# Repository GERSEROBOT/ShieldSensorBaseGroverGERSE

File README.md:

# SensorBaseGroverGERSE

If it is necessary to download the MyKiCad repository, it is a library and contains components that this project can use
	- https://github.com/pedro-ibs/MyKiCad

-------------------------------------------------------------------------------------------------------------------------------

The sensors for this shield find if the SensorBaseGrover repository
	- 123

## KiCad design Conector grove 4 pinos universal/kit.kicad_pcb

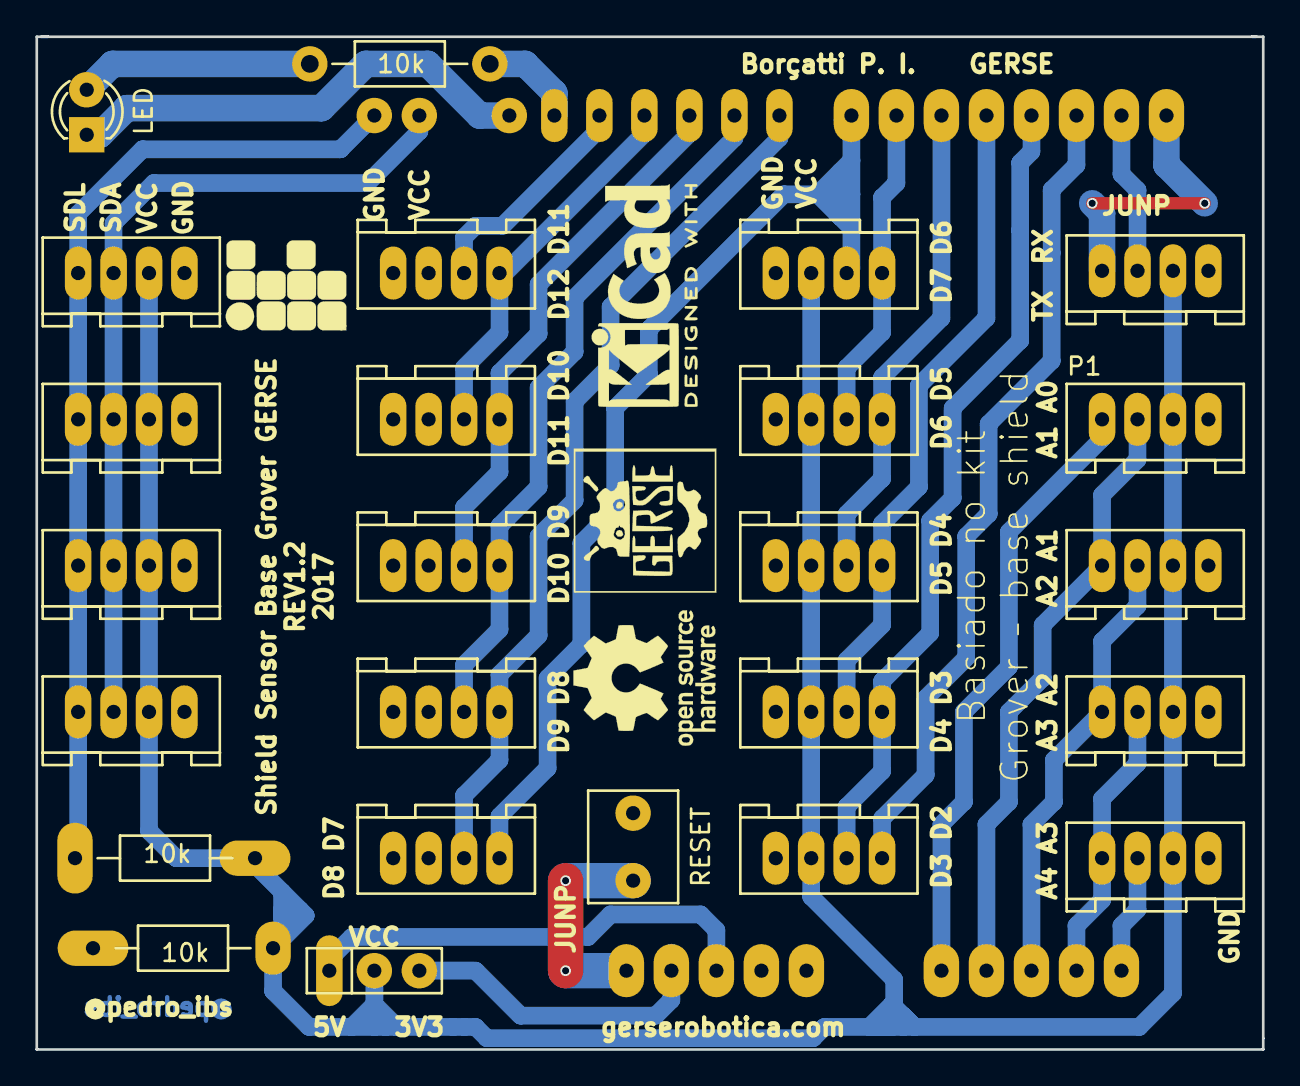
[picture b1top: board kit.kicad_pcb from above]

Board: 2 copper layers, 69.2 x 57.2 mm, 26 parts (0 on the bottom side), 26 nets.

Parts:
D1: LED; LED-3MM
IC1: ARDUINO_UNO
JP1: JUMP3; SW_Micro_SPST
P1: A0; Grove 4 pinos
P2: A1; Grove 4 pinos
P3: A2; Grove 4 pinos
P4: A3; Grove 4 pinos
P5: UART; Grove 4 pinos
P6: D2; Grove 4 pinos
P7: D3; Grove 4 pinos
P8: D4; Grove 4 pinos
P9: D5; Grove 4 pinos
P10: D6; Grove 4 pinos
P11: D7; Grove 4 pinos
P12: D8; Grove 4 pinos
P13, P14, P15, P16: I2C; Grove 4 pinos
P17: D11; Grove 4 pinos
P18: D10; Grove 4 pinos
P19: D9; Grove 4 pinos
R1, R2, R3: 10k; Resistor_Horizontal_RM10mm
SW_RS1: RESET; BUTTON2P

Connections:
3V3: IC1.3V3, JP1.3
5V: IC1.5V, JP1.1
ADC0: IC1.A0, P1.1
ADC1: IC1.A1, P1.2, P2.1
ADC2: IC1.A2, P2.2, P3.1
ADC3: IC1.A3, P3.2, P4.1
ADC4: IC1.A4, P4.2, P13.2, P14.2, P15.2, P16.2, R2.1
ADC5: IC1.A5, P13.1, P14.1, P15.1, P16.1, R1.1
D2: IC1.2, P6.1
D3: IC1.3, P6.2, P7.1
D4: IC1.4, P7.2, P8.1
D5: IC1.5, P8.2, P9.1
D6: IC1.6, P9.2, P10.1
D7: IC1.7, P10.2, P11.1
D8: IC1.8, P11.2, P12.1
D9: IC1.9, P12.2, P19.1
D10: IC1.10, P18.1, P19.2
D11: IC1.11, P17.1, P18.2
D12: IC1.12, P17.2
D13: IC1.13, R3.1
Earth: D1.1, IC1.GND, P1.4, P2.4, P3.4, P4.4, P5.4, P6.4, P7.4, P8.4, P9.4, P10.4, P11.4, P12.4, P13.4, P14.4, P15.4, P16.4, P17.4, P18.4, P19.4, SW_RS1.1
unnamed: D1.2, R3.2
RT: IC1.RT, SW_RS1.2
RXD: IC1.0, P5.1
TXD: IC1.1, P5.2
VCC: JP1.2, P1.3, P2.3, P3.3, P4.3, P5.3, P6.3, P7.3, P8.3, P9.3, P10.3, P11.3, P12.3, P13.3, P14.3, P15.3, P16.3, P17.3, P18.3, P19.3, R1.2, R2.2

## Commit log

2017-08-31 Qui Ago 31 16:26:19 BRT 2017
2017-09-04 Seg Set 4 14:45:49 BRT 2017
